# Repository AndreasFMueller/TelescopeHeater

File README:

PWM circuit to control heating elements for telescopes

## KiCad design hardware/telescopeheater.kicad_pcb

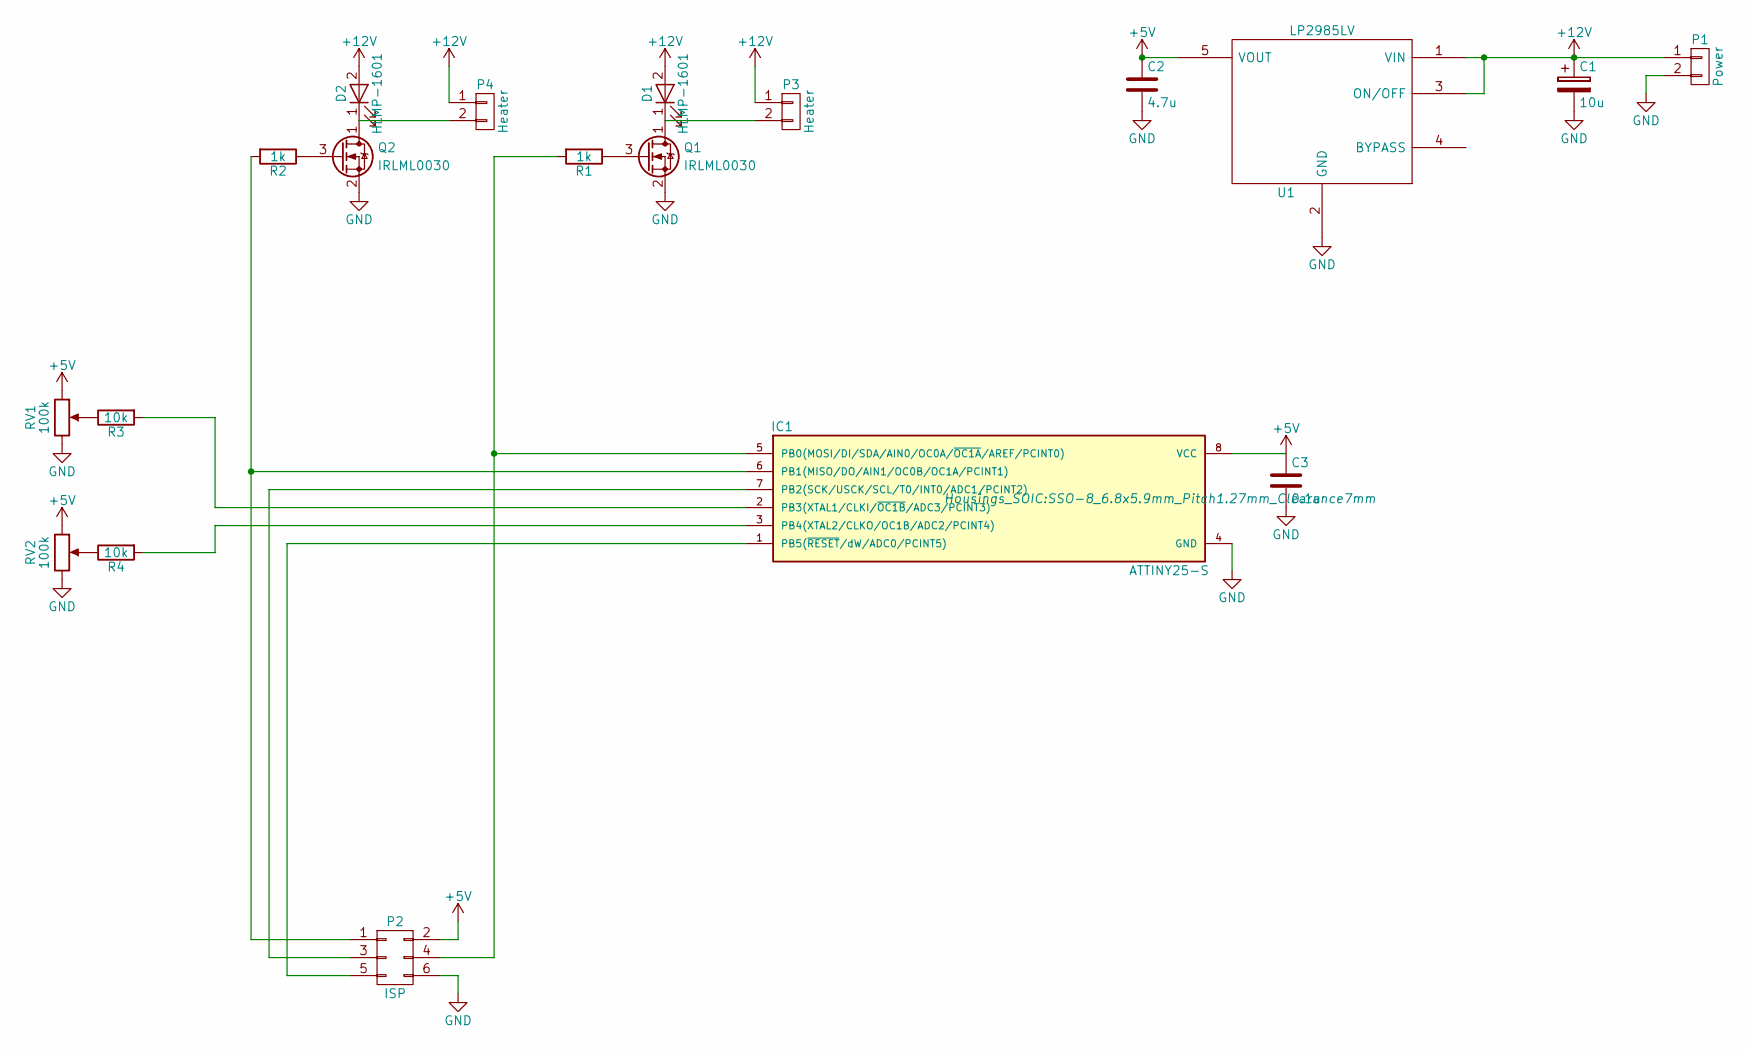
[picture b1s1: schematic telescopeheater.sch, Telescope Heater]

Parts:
C1: 10u; CP_Tantalum_Case-C_EIA-6032-28_Hand
C2: 4.7u; C_0805_HandSoldering
C3: 0.1u; C_0603_HandSoldering
D1, D2: HLMP-1601; LED_D3.0mm
IC1: ATTINY25-S; SSO-8_6.8x5.9mm_Pitch1.27mm_Clearance7mm
P1: Power
P2: ISP
P3, P4: Heater; RC-5231
Q1, Q2: IRLML0030; SOT-23-IRLM
R1, R2: 1k; R_0603_HandSoldering
R3, R4: 10k; R_0603_HandSoldering
RV1, RV2: 100k; Cermet
U1: LP2985LV; SOT-23-5_HandSoldering

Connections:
+5V: C2.1, C3.1, IC1.8 (VCC), P2.2, RV1.1, RV2.1, U1.5 (VOUT)
+12V: C1.1, D1.2 (A), D2.2 (A), P1.1, P3.1, P4.1, U1.1 (VIN), U1.3 (ON/OFF)
GND: C1.2, C2.2, C3.2, IC1.4 (GND), P1.2, P2.6, Q1.2 (S), Q2.2 (S), RV1.3, RV2.3, U1.2 (GND)
unnamed: D1.1 (K), P3.2, Q1.1 (D)
unnamed: D2.1 (K), P4.2, Q2.1 (D)
unnamed: IC1.1 (PB5(~RESET~/dW/ADC0/PCINT5)), P2.5
unnamed: IC1.2 (PB3(XTAL1/CLKI/~OC1B~/ADC3/PCINT3)), R3.2
unnamed: IC1.3 (PB4(XTAL2/CLKO/OC1B/ADC2/PCINT4)), R4.2
unnamed: IC1.5 (PB0(MOSI/DI/SDA/AIN0/OC0A/~OC1A~/AREF/P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), P2.4, R1.2
unnamed: IC1.6 (PB1(MISO/DO/AIN1/OC0B/OC1A/PCINT1)), P2.1, R2.2
unnamed: IC1.7 (PB2(SCK/USCK/SCL/T0/INT0/ADC1/PCINT2)), P2.3
unnamed: Q1.3 (G), R1.1
unnamed: Q2.3 (G), R2.1
unnamed: R3.1, RV1.2
unnamed: R4.1, RV2.2

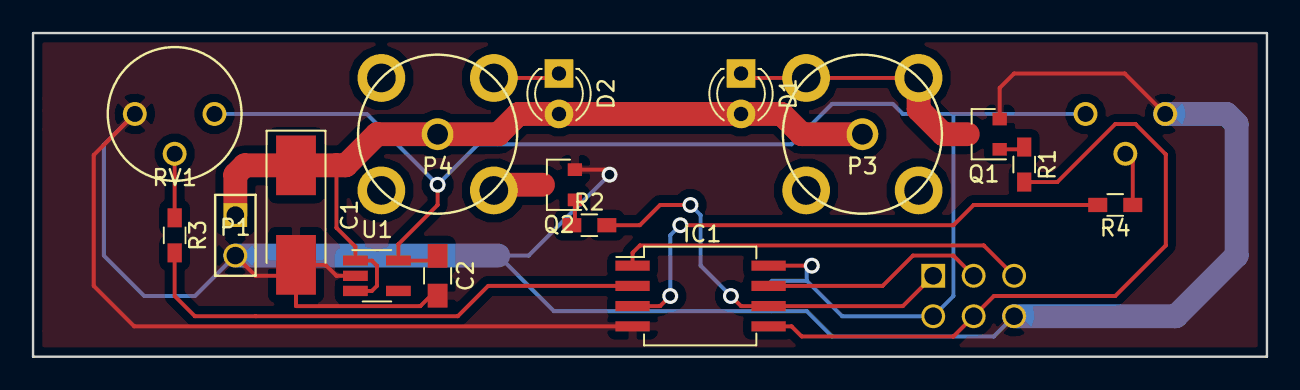
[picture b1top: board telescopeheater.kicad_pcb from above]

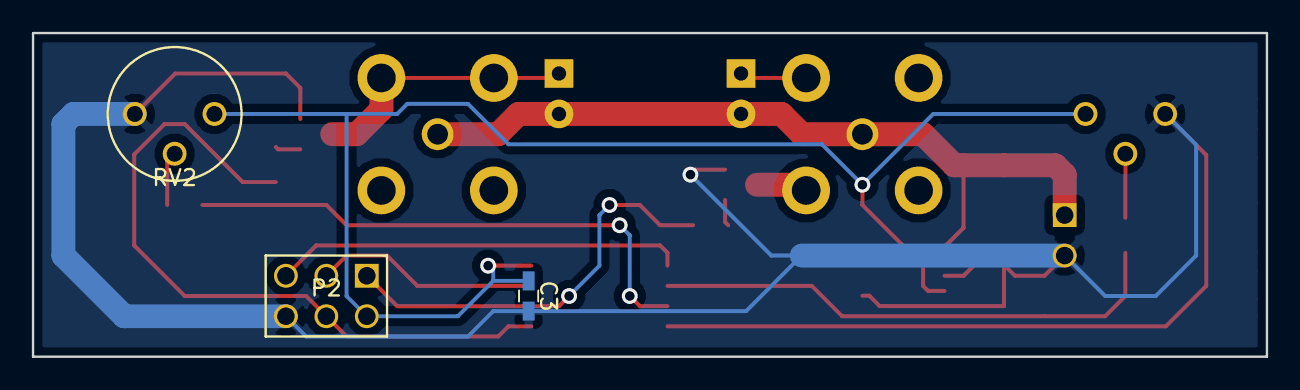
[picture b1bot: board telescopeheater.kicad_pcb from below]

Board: 2 copper layers, 77.5 x 20.3 mm, 19 parts (3 on the bottom side), 15 nets.

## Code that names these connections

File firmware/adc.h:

/*
 * adc.h -- Potentiometer auslesen
 *
 * (c) 2018 Prof Dr Andreas Müller, Hochschule Rapperswil
 */
#ifndef _adc_h
#define _adc_h

#define ADC_CHANNEL_1	0
#define ADC_CHANNEL_2	1

/*
 * The ADC inputs are assigned as follows
 *
 * RV1 -> ADC3(PB3)   controls heater output P4 (PB1, OC0B, OC1A)
 * RV2 -> ADC2(PB4)   controls heater output P3 (PB0, OC0A)
 */

/**
 * \brief initiate ADC conversion
 */
void	adc_initate(unsigned char channel);

#endif /* _adc_h */

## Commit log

2018-01-18 check in 1st version
2018-01-18 first version
2018-01-18 version for the first batch of boards
2018-01-20 Gehäuse hinzugefügt
2018-01-21 minor improvements
2018-01-21 more improvements
2018-01-22 add missing file
2018-01-24 fix dimensions of battery pack
2018-01-25 add foot
2018-01-29 add source code for firmware
2018-01-29 add datasheet
2018-01-30 firmware complete
2018-01-30 new data sheet
2018-01-30 fix MOSFET footprint
2018-03-01 fix hole positions
2018-03-02 reorganize scad code
2018-03-02 add connector model
2018-03-11 small changes to the case
2018-03-24 new parts
2019-02-09 add protection cap
